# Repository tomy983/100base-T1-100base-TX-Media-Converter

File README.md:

# 100base-T1-100base-TX-Media-Converter
PCB designed to convert automotive ethernet 100base-T1 to 100base-TX ethernet

This is a corrected version (the picture shows the previous revision). The correction consists of a missing resistor to set the TJA1101B MDIO address.

Another issue I had during bring up was the ferrite bead FB1, which I originally selected of incorrect value. (The TJA1101B was reporting low voltage on register 25 bits 15 and 14 (UV_VDDD_3V3 and UV_VDDA_3V3). I corrected it in the published schematic, but it is untested. On my PCB I've just shorted it.

I've tested 2 of this board with Unshielded and not twisted wire (ideally should be Twisted - UTP) of 8 meters length, reaching a speed of 85Mbps. No dropped packets were observed.
The polarity of the 2 wire ethernet doesn't really matter (the slave will correct accordingly).
After this successful test I've proceeded testing with my PandarQT 3D lidar (which only has 100base-T1 interface) successfully.

No MDIO setup is needed (the configuration is all done via strapping resistors). Just bridge the solder bridges to select autonomous mode and also master or slave as needed.
While not required, if you need MDIO interface to check / set registers, keep in mind that while in autonomous mode the MDIO interface of TJA1101B will not work. Just set it to managed.

Is included the very rough Arduino sketch that I've used to interface with MDIO (bit banging).

Resources used for this project:

- https://www.nxp.com/downloads/en/schematics/RDDRONE-T1ADAPT-SCH.pdf
- https://github.com/NXPHoverGames/RDDRONE-T1ADAPT/blob/main/t1eth10Lpc/src/t1eth10Lpc.c
- https://github.com/ehntoo/100base-t1-converter
- https://www.nxp.com/document/guide/getting-started-with-the-rddrone-t1adapt-evaluation-board:GS-RDDRONE-T1ADAPT
- https://github.com/cioban/arduino-projects/blob/master/smi/smi.ino

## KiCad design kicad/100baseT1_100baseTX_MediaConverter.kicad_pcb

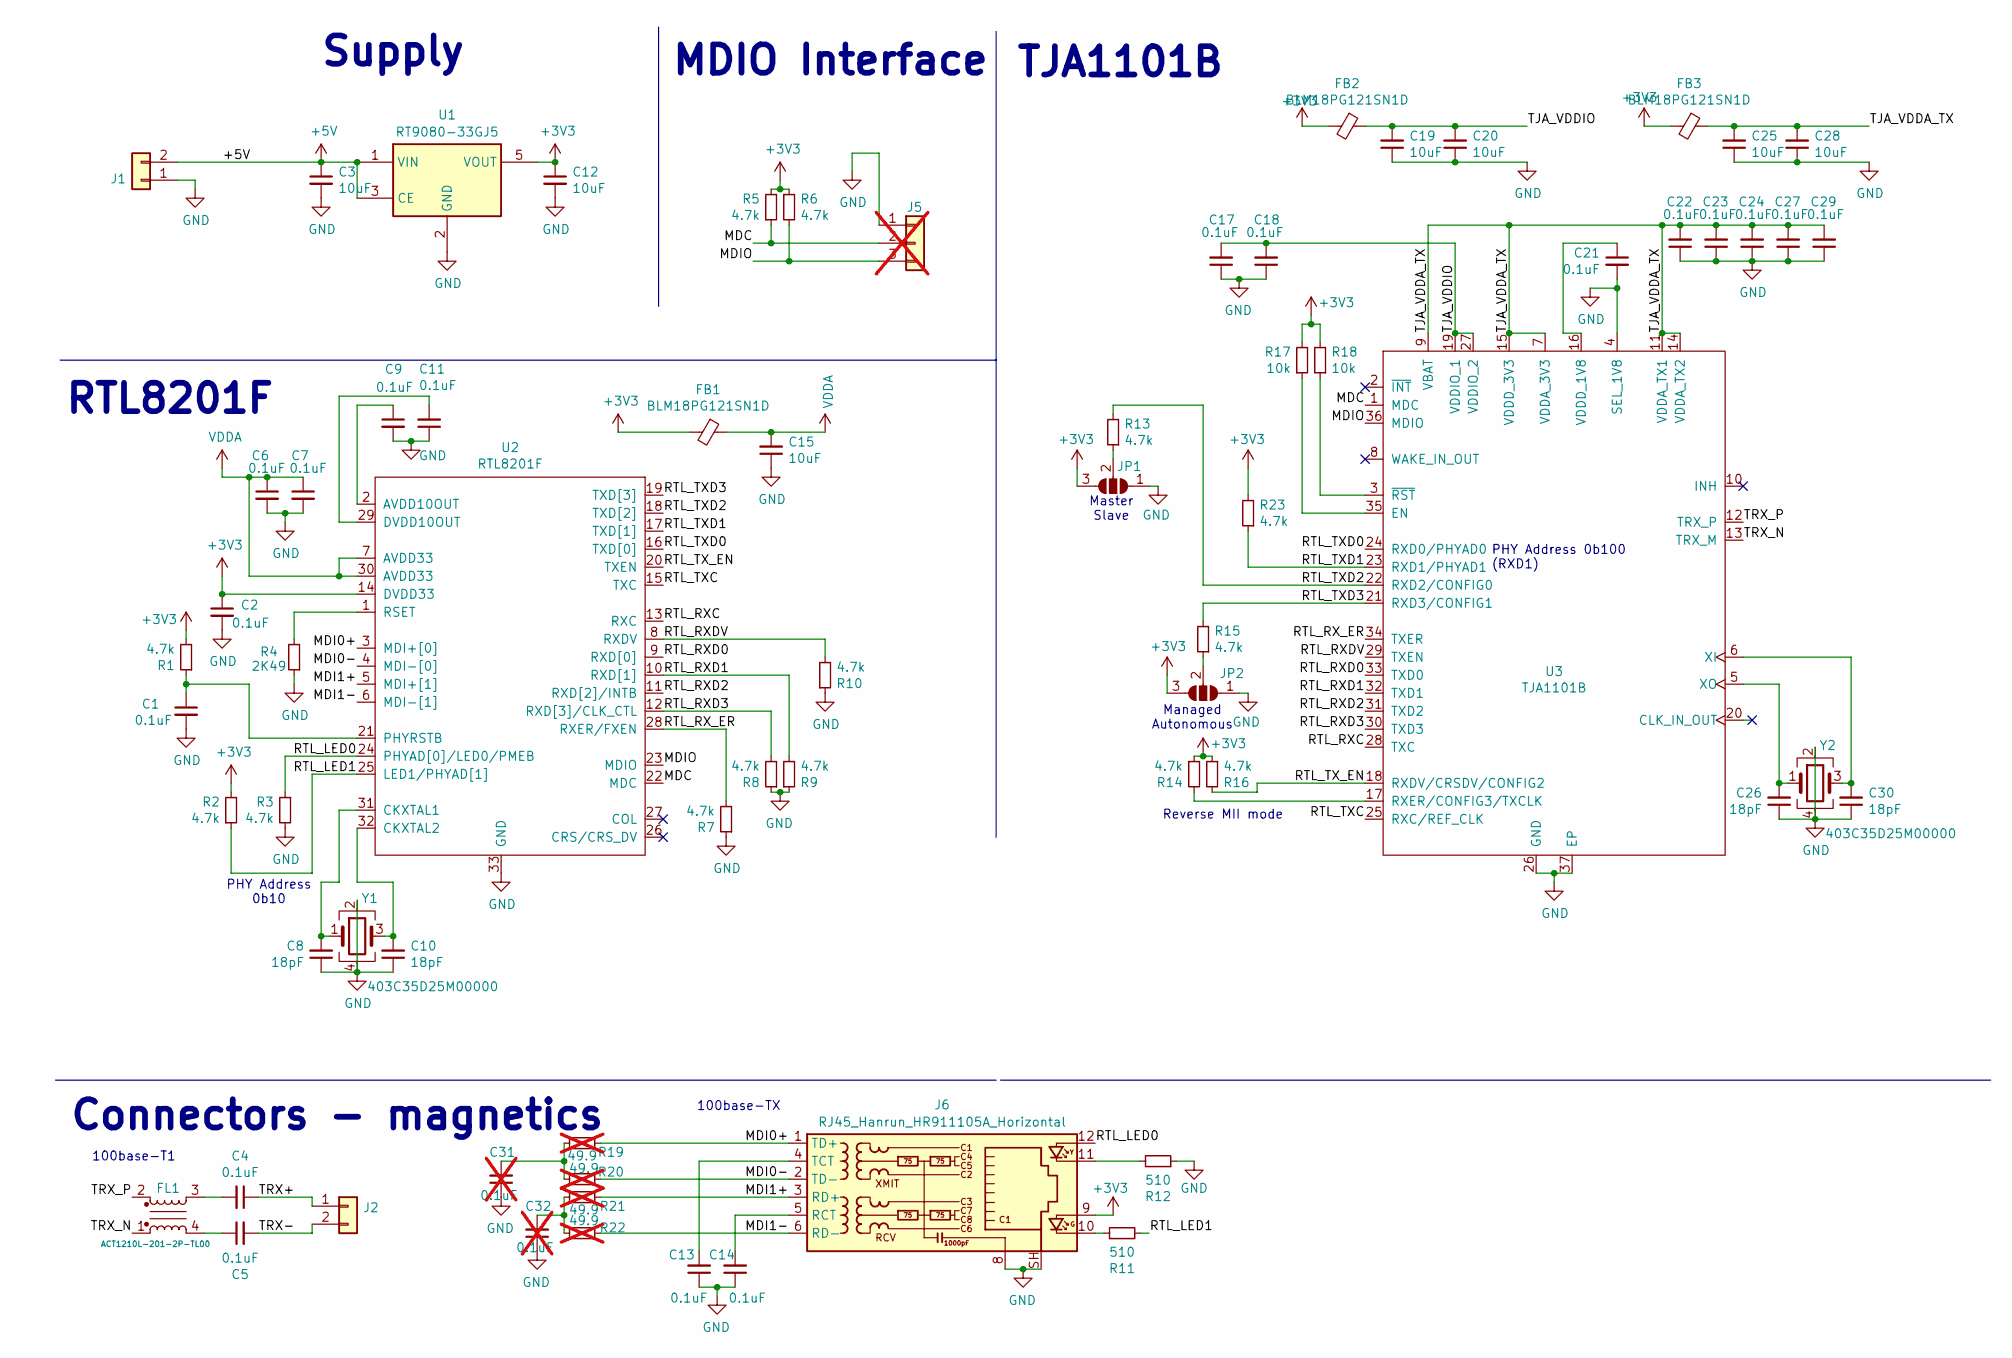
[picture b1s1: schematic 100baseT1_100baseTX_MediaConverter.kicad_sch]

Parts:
C1, C2, C4, C5, C6, C7, C9, C11, C13, C14, C17, C18, C21, C22, C23, C24, C27, C29: 0.1uF; C_0603_1608Metric
C3, C12, C15, C19, C20, C25, C28: 10uF; C_0603_1608Metric
C8, C10, C26, C30: 18pF; C_0603_1608Metric
C31, C32: 0.1uF; C_0603_1608Metric; not fitted
FB1, FB2, FB3: BLM18PG121SN1D; L_0603_1608Metric
FL1: ACT1210L-201-2P-TL00; ACT1210L
J1, J2: Conn_01x02; PinHeader_1x02_P2.54mm_Vertical
J5: Conn_01x03; PinHeader_1x03_P2.54mm_Vertical; not fitted
J6: RJ45_Hanrun_HR911105A_Horizontal
JP1, JP2: SolderJumper_3_Open; SolderJumper-3_P1.3mm_Open_RoundedPad1.0x1.5mm_NumberLabels
R1, R2, R3, R5, R6, R7, R8, R9, R10, R13, R14, R15, R16, R23: 4.7k; R_0603_1608Metric
R4: 2K49; R_0603_1608Metric
R11, R12: 510; R_0603_1608Metric
R17, R18: 10k; R_0603_1608Metric
R19, R20, R21, R22: 49.9; R_0603_1608Metric; not fitted
U1: RT9080-33GJ5; SOT-23-5; MPN XC6210B332MR-G
U2: RTL8201F; QFN-32-1EP_5x5mm_P0.5mm_EP3.3x3.3mm_ThermalVias
U3: TJA1101B; QFN-36-1EP_6x6mm_P0.5mm_EP3.7x3.7mm_ThermalVias
Y1, Y2: 403C35D25M00000; Crystal_SMD_SeikoEpson_FA238V-4Pin_3.2x2.5mm

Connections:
+3V3: C2.1, C12.1, FB1.2, FB2.2, FB3.2, J6.9, JP1.3 (B), JP2.3 (B), R1.2, R2.2, R5.2, R6.1, R14.1, R16.1, R17.2, R18.2, R23.2, U1.5 (VOUT), U2.14 (DVDD33)
+5V: C3.1, J1.2, U1.1 (VIN), U1.3 (CE)
/MDC: J5.2, R5.1, U2.22 (MDC), U3.1 (MDC)
/MDI0+: J6.1 (TD+), R19.2, U2.3 (MDI+[0])
/MDI0-: J6.2 (TD-), R20.2, U2.4 (MDI-[0])
/MDI1+: J6.3 (RD+), R21.2, U2.5 (MDI+[1])
/MDI1-: J6.6 (RD-), R22.2, U2.6 (MDI-[1])
/MDIO: J5.3, R6.2, U2.23 (MDIO), U3.36 (MDIO)
/RTL_LED0: J6.12, R3.1, U2.24 (PHYAD[0]/LED0/PMEB)
/RTL_LED1: R2.1, R11.2, U2.25 (LED1/PHYAD[1])
/RTL_RXC: U2.13 (RXC), U3.28 (TXC)
/RTL_RXD0: U2.9 (RXD[0]), U3.33 (TXD0)
/RTL_RXD1: R9.2, U2.10 (RXD[1]), U3.32 (TXD1)
/RTL_RXD2: U2.11 (RXD[2]/INTB), U3.31 (TXD2)
/RTL_RXD3: R8.2, U2.12 (RXD[3]/CLK_CTL), U3.30 (TXD3)
/RTL_RXDV: R10.2, U2.8 (RXDV), U3.29 (TXEN)
/RTL_RX_ER: R7.2, U2.28 (RXER/FXEN), U3.34 (TXER)
/RTL_TXC: U2.15 (TXC), U3.25 (RXC/REF_CLK)
/RTL_TXD0: U2.16 (TXD[0]), U3.24 (RXD0/PHYAD0)
/RTL_TXD1: R23.1, U2.17 (TXD[1]), U3.23 (RXD1/PHYAD1)
/RTL_TXD2: R13.2, U2.18 (TXD[2]), U3.22 (RXD2/CONFIG0)
/RTL_TXD3: R15.2, U2.19 (TXD[3]), U3.21 (RXD3/CONFIG1)
/RTL_TX_EN: R16.2, U2.20 (TXEN), U3.18 (RXDV/CRSDV/CONFIG2)
/TJA_VDDA_TX: C22.2, C23.2, C24.2, C25.2, C27.2, C28.2, C29.2, FB3.1, U3.7 (VDDA_3V3), U3.9 (VBAT), U3.11 (VDDA_TX1), U3.14 (VDDA_TX2), U3.15 (VDDD_3V3)
/TJA_VDDIO: C17.2, C18.2, C19.2, C20.2, FB2.1, U3.19 (VDDIO_1), U3.27 (VDDIO_2)
/TRX+: C4.1, J2.1
/TRX-: C5.2, J2.2
/TRX_N: FL1.1, U3.13 (TRX_M)
/TRX_P: FL1.2, U3.12 (TRX_P)
GND: C1.2, C2.2, C3.2, C6.2, C7.2, C8.1, C9.2, C10.1, C11.1, C12.2, C13.1, C14.1, C15.1, C17.1, C18.1, C19.1, C20.1, C21.2, C22.1, C23.1, C24.1, C25.1, C26.1, C27.1, C28.1, C29.1, C30.1, C31.1, C32.1, J1.1, J5.1, J6.8, J6.SH, JP1.1 (A), JP2.1 (A), R3.2, R4.1, R7.1, R8.1, R9.1, R10.1, R12.1, U1.2 (GND), U2.33 (GND), U3.4 (SEL_1V8), U3.26 (GND), U3.37 (EP), Y1.2, Y1.4, Y2.2, Y2.4
unnamed: C4.2, FL1.3
unnamed: C5.1, FL1.4
unnamed: C31.2, R19.1, R20.1
unnamed: C32.2, R21.1, R22.1
unnamed: J6.10, R11.1
unnamed: J6.11, R12.2
unnamed: C14.2, J6.5 (RCT)
unnamed: C13.2, J6.4 (TCT)
unnamed: JP1.2 (C), R13.1
unnamed: JP2.2 (C), R15.1
unnamed: C9.1, U2.2 (AVDD10OUT)
unnamed: C8.2, U2.31 (CKXTAL1), Y1.1
unnamed: C10.2, U2.32 (CKXTAL2), Y1.3
unnamed: C11.2, U2.29 (DVDD10OUT)
unnamed: C1.1, R1.1, U2.21 (PHYRSTB)
unnamed: R4.2, U2.1 (RSET)
unnamed: R17.1, U3.35 (EN)
unnamed: R14.2, U3.17 (RXER/CONFIG3/TXCLK)
unnamed: C21.1, U3.16 (VDDD_1V8)
unnamed: C30.2, U3.6 (XI), Y2.3
unnamed: C26.2, U3.5 (XO), Y2.1
unnamed: R18.1, U3.3 (~RST)
VDDA: C6.1, C7.1, C15.2, FB1.1, U2.7 (AVDD33), U2.30 (AVDD33)

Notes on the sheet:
100base-T1
Connectors - magnetics
PHY Address 0b100 (RXD1)
MDIO Interface
TJA1101B
Master Slave
Reverse MII mode
RTL8201F
100base-TX
Managed Autonomous
PHY Address 0b10
Supply

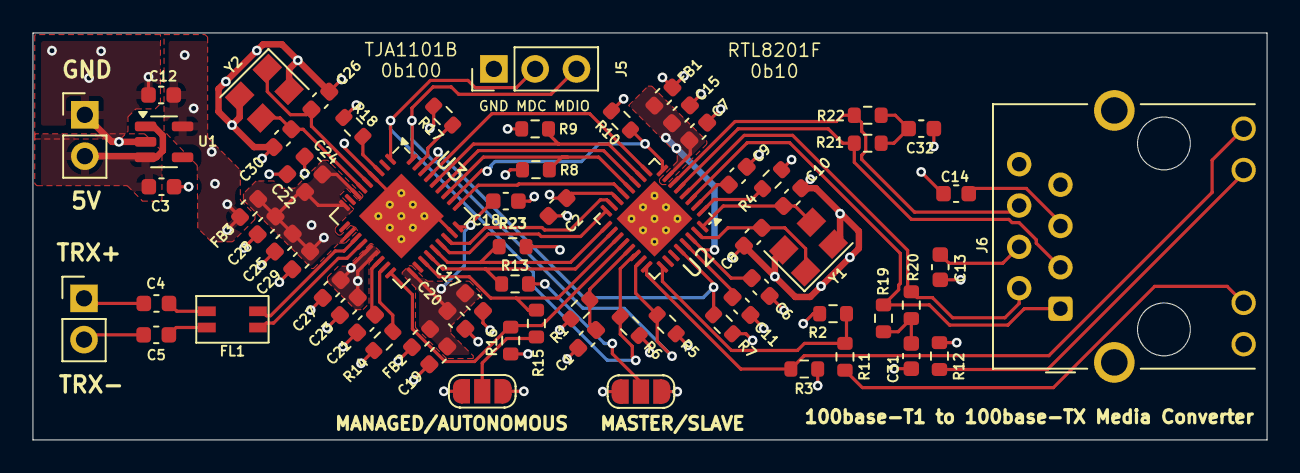
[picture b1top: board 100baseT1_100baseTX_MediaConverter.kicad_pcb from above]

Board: 4 copper layers, 75.9 x 25.0 mm, 69 parts (0 on the bottom side), 53 nets.

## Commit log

2025-06-02 Rename Immagine WhatsApp 2025-06-02 ore 14.37.47_8be051e5.jpg to picture.jpg
2025-06-02 Rename Screenshot 2025-06-02 143416.png to render.png
2025-06-02 Rename 100baseT1_100baseTX_Media_Converter.pdf to Schematic.pdf
2025-06-02 Rename 100baseT1_100baseTX_MediaConverter.kicad_pro to kicad/100baseT1_100baseTX_MediaConverter.kicad_pro
2025-06-02 Rename RTL8201F-VB-CG.pdf to docs/RTL8201F-VB-CG.pdf
2025-06-02 Rename TJA1101B.pdf to docs/TJA1101B.pdf
2025-06-02 Rename SMI-MDIO.ino to arduino/SMI-MDIO.ino
2025-06-02 Rename picture.jpg to images/picture.jpg
2025-06-02 Rename render.png to images/render.png
